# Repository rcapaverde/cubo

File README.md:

# cubo - um processador conceitual

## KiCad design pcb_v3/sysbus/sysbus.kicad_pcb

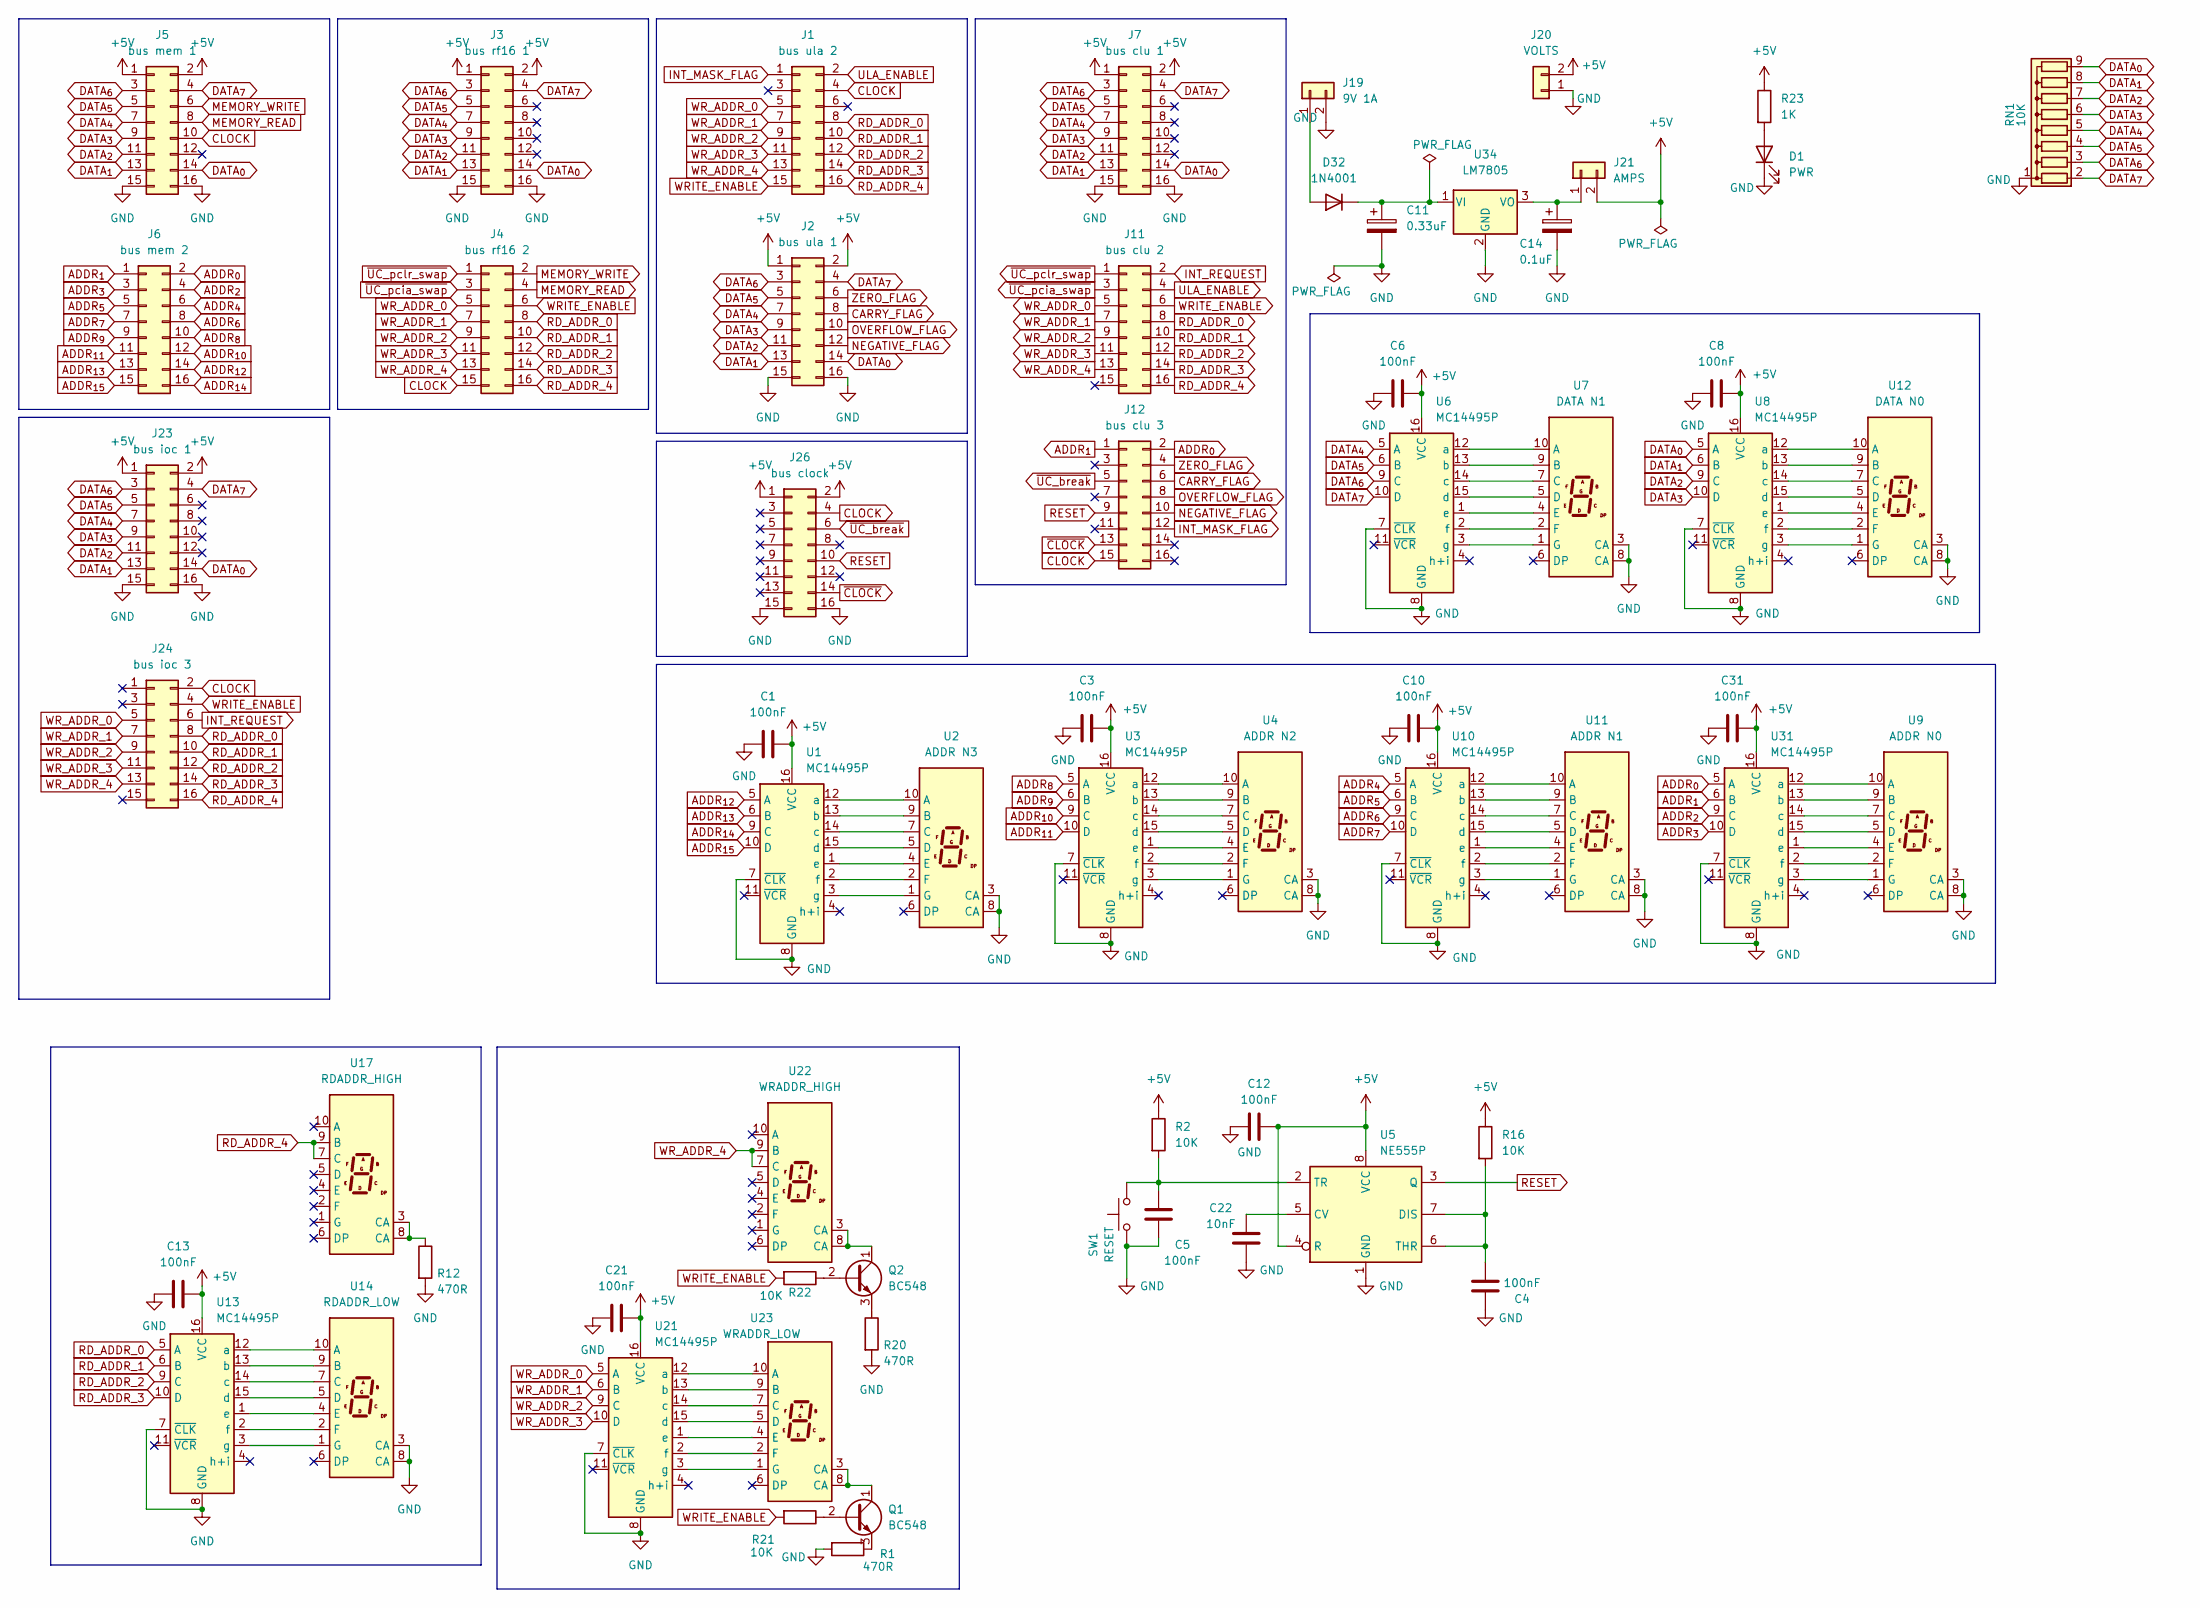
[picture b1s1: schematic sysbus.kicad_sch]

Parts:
C1, C3, C6, C8, C10, C13, C21, C31: 100nF; C_Disc_D5.1mm_W3.2mm_P5.00mm
C4, C5, C12: 100nF; C_Disc_D4.7mm_W2.5mm_P5.00mm
C11: 0.33uF; CP_Radial_D5.0mm_P2.50mm
C14: 0.1uF; CP_Radial_D5.0mm_P2.50mm
C22: 10nF; C_Disc_D4.7mm_W2.5mm_P5.00mm
D1: PWR; LED_D5.0mm
D32: 1N4001; D_DO-41_SOD81_P10.16mm_Horizontal
J1: bus ula 2; conector 02x08
J2: bus ula 1; conector 02x08
J3: bus rf16 1; conector 02x08
J4: bus rf16 2; conector 02x08
J5: bus mem 1; conector 02x08
J6: bus mem 2; conector 02x08
J7: bus clu 1; conector 02x08
J11: bus clu 2; conector 02x08
J12: bus clu 3; conector 02x08
J19: 9V 1A; JST_XH_B2B-XH-A_1x02_P2.50mm_Vertical
J20: VOLTS; JST_XH_B2B-XH-A_1x02_P2.50mm_Vertical
J21: AMPS; JST_XH_B2B-XH-A_1x02_P2.50mm_Vertical
J23: bus ioc 1; conector 02x08
J24: bus ioc 3; conector 02x08
J26: bus clock; conector 02x08
Q1, Q2: BC548; TO-92_Inline
R1, R12, R20: 470R; R_Axial_DIN0207_L6.3mm_D2.5mm_P7.62mm_Horizontal
R2, R16, R21, R22: 10K; R_Axial_DIN0207_L6.3mm_D2.5mm_P7.62mm_Horizontal
R23: 1K; R_Axial_DIN0207_L6.3mm_D2.5mm_P7.62mm_Horizontal
RN1: 10K; R_Array_SIP9
SW1: RESET; JST_XH_B2B-XH-A_1x02_P2.50mm_Vertical
U1, U3, U6, U8, U10, U13, U21, U31: MC14495P; DIP-16_W7.62mm
U2: ADDR N3; Sx39-1xxxxx
U4: ADDR N2; Sx39-1xxxxx
U5: NE555P; DIP-8_W7.62mm
U7: DATA N1; Sx39-1xxxxx
U9: ADDR N0; Sx39-1xxxxx
U11: ADDR N1; Sx39-1xxxxx
U12: DATA N0; Sx39-1xxxxx
U14: RDADDR_LOW; Sx39-1xxxxx
U17: RDADDR_HIGH; Sx39-1xxxxx
U22: WRADDR_HIGH; Sx39-1xxxxx
U23: WRADDR_LOW; Sx39-1xxxxx
U34: LM7805; TO-220-3_Vertical

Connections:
+5V: C1.2, C3.2, C6.2, C8.2, C10.2, C12.2, C13.2, C21.2, C31.2, J2.1, J2.2, J3.1, J3.2, J5.1, J5.2, J7.1, J7.2, J20.2, J21.2, J23.1, J23.2, J26.1, J26.2, R2.1, R16.1, R23.1, U1.16 (VCC), U3.16 (VCC), U5.4 (R), U5.8 (VCC), U6.16 (VCC), U8.16 (VCC), U10.16 (VCC), U13.16 (VCC), U21.16 (VCC), U31.16 (VCC)
ADDR_{0}: J6.2, J12.2, U31.5 (A)
ADDR_{1}: J6.1, J12.1, U31.6 (B)
ADDR_{2}: J6.4, U31.9 (C)
ADDR_{3}: J6.3, U31.10 (D)
ADDR_{4}: J6.6, U10.5 (A)
ADDR_{5}: J6.5, U10.6 (B)
ADDR_{6}: J6.8, U10.9 (C)
ADDR_{7}: J6.7, U10.10 (D)
ADDR_{8}: J6.10, U3.5 (A)
ADDR_{9}: J6.9, U3.6 (B)
ADDR_{10}: J6.12, U3.9 (C)
ADDR_{11}: J6.11, U3.10 (D)
ADDR_{12}: J6.14, U1.5 (A)
ADDR_{13}: J6.13, U1.6 (B)
ADDR_{14}: J6.16, U1.9 (C)
ADDR_{15}: J6.15, U1.10 (D)
CARRY_FLAG: J2.8, J12.6
CLOCK: J1.4, J4.15, J5.10, J12.15, J24.2, J26.4
DATA_{0}: J2.14, J3.14, J5.14, J7.14, J23.14, RN1.9 (R8), U8.5 (A)
DATA_{1}: J2.13, J3.13, J5.13, J7.13, J23.13, RN1.8 (R7), U8.6 (B)
DATA_{2}: J2.11, J3.11, J5.11, J7.11, J23.11, RN1.7 (R6), U8.9 (C)
DATA_{3}: J2.9, J3.9, J5.9, J7.9, J23.9, RN1.6 (R5), U8.10 (D)
DATA_{4}: J2.7, J3.7, J5.7, J7.7, J23.7, RN1.5 (R4), U6.5 (A)
DATA_{5}: J2.5, J3.5, J5.5, J7.5, J23.5, RN1.4 (R3), U6.6 (B)
DATA_{6}: J2.3, J3.3, J5.3, J7.3, J23.3, RN1.3 (R2), U6.9 (C)
DATA_{7}: J2.4, J3.4, J5.4, J7.4, J23.4, RN1.2 (R1), U6.10 (D)
GND: C1.1, C3.1, C4.1, C5.1, C6.1, C8.1, C10.1, C11.2, C12.1, C13.1, C14.2, C21.1, C22.1, C31.1, D1.1 (K), J2.15, J2.16, J3.15, J3.16, J5.15, J5.16, J7.15, J7.16, J19.2, J20.1, J23.15, J23.16, J26.15, J26.16, R1.2, R12.2, R20.2, RN1.1 (common), SW1.1, U1.7 (~CLK), U1.8 (GND), U2.3 (CA), U2.8 (CA), U3.7 (~CLK), U3.8 (GND), U4.3 (CA), U4.8 (CA), U5.1 (GND), U6.7 (~CLK), U6.8 (GND), U7.3 (CA), U7.8 (CA), U8.7 (~CLK), U8.8 (GND), U9.3 (CA), U9.8 (CA), U10.7 (~CLK), U10.8 (GND), U11.3 (CA), U11.8 (CA), U12.3 (CA), U12.8 (CA), U13.7 (~CLK), U13.8 (GND), U14.3 (CA), U14.8 (CA), U21.7 (~CLK), U21.8 (GND), U31.7 (~CLK), U31.8 (GND), U34.2 (GND)
INT_MASK_FLAG: J1.1, J12.12
INT_REQUEST: J11.2, J24.6
MEMORY_READ: J4.4, J5.8
MEMORY_WRITE: J4.2, J5.6
NEGATIVE_FLAG: J2.12, J12.10
unnamed: D1.2 (A), R23.2
unnamed: D32.2 (A), J19.1
unnamed: C11.1, D32.1 (K), U34.1 (VI)
unnamed: C14.1, J21.1, U34.3 (VO)
unnamed: Q1.2 (B), R21.1
unnamed: Q1.1 (C), U23.3 (CA), U23.8 (CA)
unnamed: Q1.3 (E), R1.1
unnamed: Q2.2 (B), R22.1
unnamed: Q2.1 (C), U22.3 (CA), U22.8 (CA)
unnamed: Q2.3 (E), R20.1
unnamed: R12.1, U17.3 (CA), U17.8 (CA)
unnamed: U1.12 (a), U2.10 (A)
unnamed: U1.13 (b), U2.9 (B)
unnamed: U1.14 (c), U2.7 (C)
unnamed: U1.15 (d), U2.5 (D)
unnamed: U1.1 (e), U2.4 (E)
unnamed: U1.2 (f), U2.2 (F)
unnamed: U1.3 (g), U2.1 (G)
unnamed: U3.12 (a), U4.10 (A)
unnamed: U3.13 (b), U4.9 (B)
unnamed: U3.14 (c), U4.7 (C)
unnamed: U3.15 (d), U4.5 (D)
unnamed: U3.1 (e), U4.4 (E)
unnamed: U3.2 (f), U4.2 (F)
unnamed: U3.3 (g), U4.1 (G)
unnamed: C22.2, U5.5 (CV)
unnamed: C4.2, R16.2, U5.6 (THR), U5.7 (DIS)
unnamed: C5.2, R2.2, SW1.2, U5.2 (TR)
unnamed: U6.12 (a), U7.10 (A)
unnamed: U6.13 (b), U7.9 (B)
unnamed: U6.14 (c), U7.7 (C)
unnamed: U6.15 (d), U7.5 (D)
unnamed: U6.1 (e), U7.4 (E)
unnamed: U6.2 (f), U7.2 (F)
unnamed: U6.3 (g), U7.1 (G)
unnamed: U10.12 (a), U11.10 (A)
unnamed: U10.13 (b), U11.9 (B)
unnamed: U10.14 (c), U11.7 (C)
unnamed: U10.15 (d), U11.5 (D)
unnamed: U10.1 (e), U11.4 (E)
unnamed: U10.2 (f), U11.2 (F)
unnamed: U10.3 (g), U11.1 (G)
unnamed: U8.12 (a), U12.10 (A)
unnamed: U8.13 (b), U12.9 (B)
unnamed: U8.14 (c), U12.7 (C)
unnamed: U8.15 (d), U12.5 (D)
unnamed: U8.1 (e), U12.4 (E)
unnamed: U8.2 (f), U12.2 (F)
unnamed: U8.3 (g), U12.1 (G)
unnamed: U13.12 (a), U14.10 (A)
unnamed: U13.13 (b), U14.9 (B)
unnamed: U13.14 (c), U14.7 (C)
unnamed: U13.15 (d), U14.5 (D)
unnamed: U13.1 (e), U14.4 (E)
unnamed: U13.2 (f), U14.2 (F)
unnamed: U13.3 (g), U14.1 (G)
unnamed: U21.12 (a), U23.10 (A)
unnamed: U21.13 (b), U23.9 (B)
unnamed: U21.14 (c), U23.7 (C)
unnamed: U21.15 (d), U23.5 (D)
unnamed: U21.1 (e), U23.4 (E)
unnamed: U21.2 (f), U23.2 (F)
unnamed: U21.3 (g), U23.1 (G)
unnamed: U9.10 (A), U31.12 (a)
unnamed: U9.9 (B), U31.13 (b)
unnamed: U9.7 (C), U31.14 (c)
unnamed: U9.5 (D), U31.15 (d)
unnamed: U9.4 (E), U31.1 (e)
unnamed: U9.2 (F), U31.2 (f)
unnamed: U9.1 (G), U31.3 (g)
OVERFLOW_FLAG: J2.10, J12.8
RD_ADDR_0: J1.8, J4.8, J11.8, J24.8, U13.5 (A)
RD_ADDR_1: J1.10, J4.10, J11.10, J24.10, U13.6 (B)
RD_ADDR_2: J1.12, J4.12, J11.12, J24.12, U13.9 (C)
RD_ADDR_3: J1.14, J4.14, J11.14, J24.14, U13.10 (D)
RD_ADDR_4: J1.16, J4.16, J11.16, J24.16, U17.7 (C), U17.9 (B)
RESET: J12.9, J26.10, U5.3 (Q)
ULA_ENABLE: J1.2, J11.4
WRITE_ENABLE: J1.15, J4.6, J11.6, J24.4, R21.2, R22.2
WR_ADDR_0: J1.5, J4.5, J11.5, J24.5, U21.5 (A)
WR_ADDR_1: J1.7, J4.7, J11.7, J24.7, U21.6 (B)
WR_ADDR_2: J1.9, J4.9, J11.9, J24.9, U21.9 (C)
WR_ADDR_3: J1.11, J4.11, J11.11, J24.11, U21.10 (D)
WR_ADDR_4: J1.13, J4.13, J11.13, J24.13, U22.7 (C), U22.9 (B)
ZERO_FLAG: J2.6, J12.4
~CLOCK: J12.13, J26.14
~UC_break: J12.5, J26.6
~UC_pcia_swap: J4.3, J11.3
~UC_pclr_swap: J4.1, J11.1

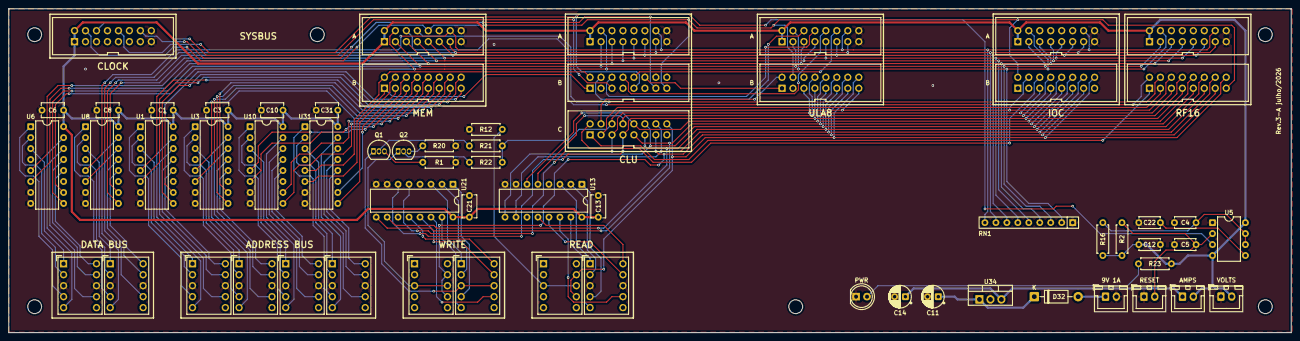
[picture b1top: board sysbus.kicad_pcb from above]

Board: 2 copper layers, 297.0 x 75.0 mm, 63 parts (0 on the bottom side), 122 nets.

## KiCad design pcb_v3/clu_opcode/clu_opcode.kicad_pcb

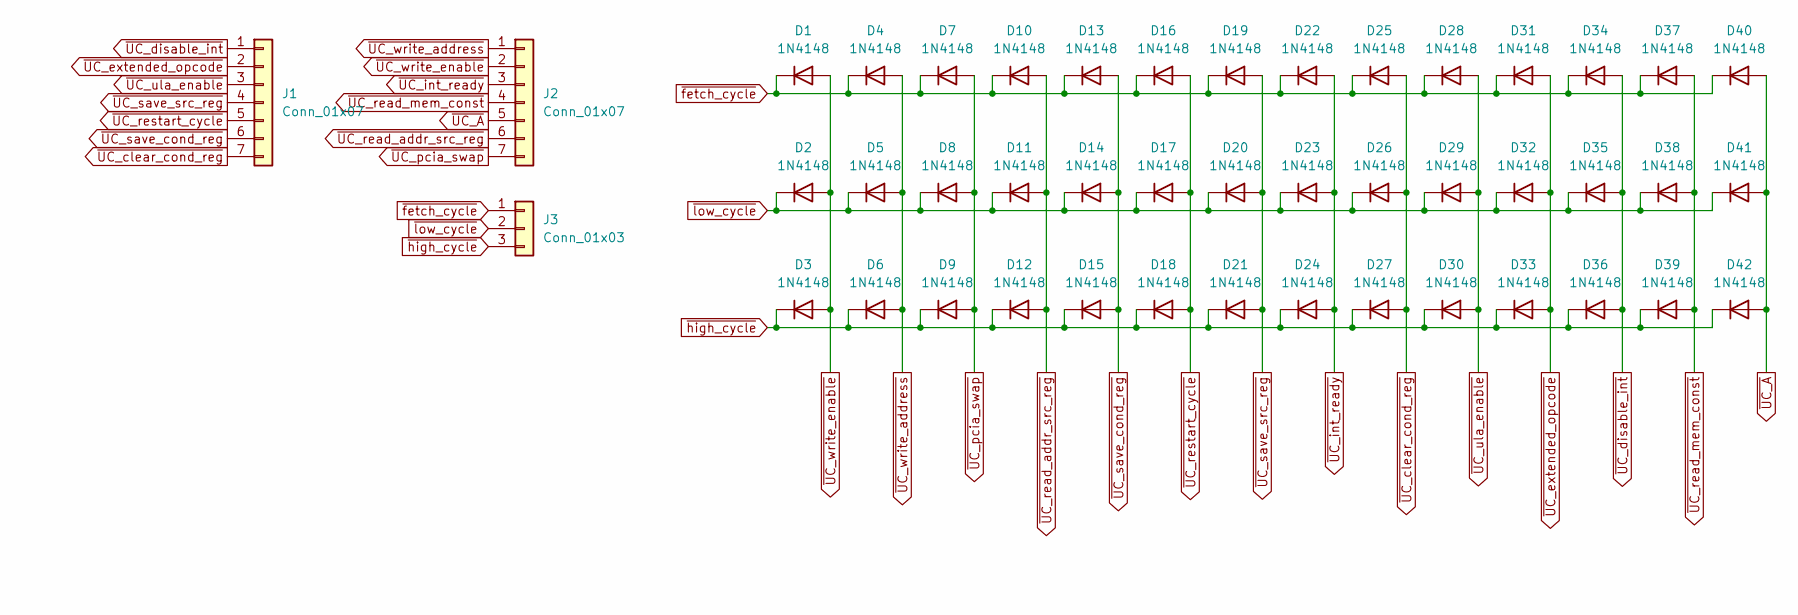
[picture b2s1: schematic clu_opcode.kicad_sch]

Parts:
D1, D2, D3, D4, D5, D6, D7, D8, D9, D10, D11, D12, D13, D14, D15, D16, D17, D18, D19, D20, D21, D22, D23, D24, D25, D26, D27, D28, D29, D30, D31, D32, D33, D34, D35, D36, D37, D38, D39, D40, D41, D42: 1N4148; D_DO-35_SOD27_P2.54mm_Vertical_AnodeUp
J1, J2: Conn_01x07; PinHeader_1x07_P2.54mm_Vertical
J3: Conn_01x03; PinHeader_1x03_P2.54mm_Vertical

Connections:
~UC_A: D40.2 (A), D41.2 (A), D42.2 (A), J2.5
~UC_clear_cond_reg: D25.2 (A), D26.2 (A), D27.2 (A), J1.7
~UC_disable_int: D34.2 (A), D35.2 (A), D36.2 (A), J1.1
~UC_extended_opcode: D31.2 (A), D32.2 (A), D33.2 (A), J1.2
~UC_int_ready: D22.2 (A), D23.2 (A), D24.2 (A), J2.3
~UC_pcia_swap: D7.2 (A), D8.2 (A), D9.2 (A), J2.7
~UC_read_addr_src_reg: D10.2 (A), D11.2 (A), D12.2 (A), J2.6
~UC_read_mem_const: D37.2 (A), D38.2 (A), D39.2 (A), J2.4
~UC_restart_cycle: D16.2 (A), D17.2 (A), D18.2 (A), J1.5
~UC_save_cond_reg: D13.2 (A), D14.2 (A), D15.2 (A), J1.6
~UC_save_src_reg: D19.2 (A), D20.2 (A), D21.2 (A), J1.4
~UC_ula_enable: D28.2 (A), D29.2 (A), D30.2 (A), J1.3
~UC_write_address: D4.2 (A), D5.2 (A), D6.2 (A), J2.1
~UC_write_enable: D1.2 (A), D2.2 (A), D3.2 (A), J2.2
~fetch_cycle: D1.1 (K), D4.1 (K), D7.1 (K), D10.1 (K), D13.1 (K), D16.1 (K), D19.1 (K), D22.1 (K), D25.1 (K), D28.1 (K), D31.1 (K), D34.1 (K), D37.1 (K), D40.1 (K), J3.1
~high_cycle: D3.1 (K), D6.1 (K), D9.1 (K), D12.1 (K), D15.1 (K), D18.1 (K), D21.1 (K), D24.1 (K), D27.1 (K), D30.1 (K), D33.1 (K), D36.1 (K), D39.1 (K), D42.1 (K), J3.3
~low_cycle: D2.1 (K), D5.1 (K), D8.1 (K), D11.1 (K), D14.1 (K), D17.1 (K), D20.1 (K), D23.1 (K), D26.1 (K), D29.1 (K), D32.1 (K), D35.1 (K), D38.1 (K), D41.1 (K), J3.2

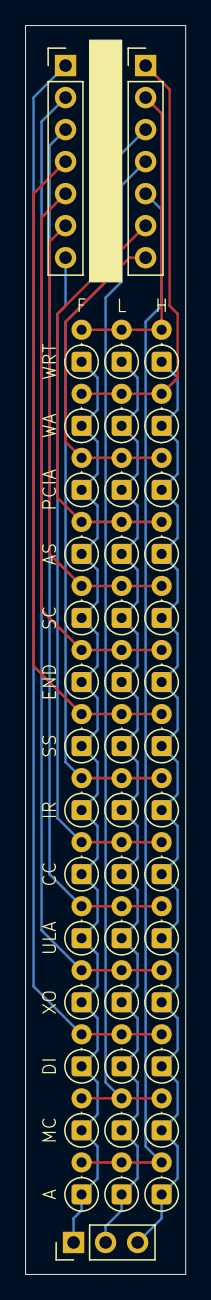
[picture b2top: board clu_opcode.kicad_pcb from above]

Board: 2 copper layers, 12.7 x 99.1 mm, 45 parts (0 on the bottom side), 17 nets.
